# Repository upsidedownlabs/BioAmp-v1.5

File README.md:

# BioAmp v1.5

BioAmp v1.5 is a single chip Bio-potential amplifier for recording any Bio-potential signal non-invasively. It's compatible with [Backyard Brains Spike Recorder](https://backyardbrains.com/products/spikerecorder), which you can use to record and visualize all the Bio-potential signals. 

## Hardware

BioAmp v1.5 has been created using [KiCad](https://www.kicad.org/) and all the design files can be found under [hardware](hardware/) folder, including production [Gerber](hardware/gerbers) files. Images below shows a quick overview of the hardware design.

| Front             |  Back |
| :-------------------------: | :-------------------------: |
|   |  |

|Assembled PCB|
|:--:|
||

| Dimensions             |  Schematic  |
| :-------------------------: | :-------------------------: |
| 32x60mm  |  |

| Licenses Facts              |  OSHWA Certification |
| :-------------------------: | :-------------------------: |
|   |  |

## License
#### Hardware
CERN Open Hardware License Version 2 - Strongly Reciprocal ([CERN-OHL-S-2.0](https://spdx.org/licenses/CERN-OHL-S-2.0.html)).

#### Software
MIT open source [license](http://opensource.org/licenses/MIT).

#### Documentation:
<br />This work is licensed under a <a rel="license" href="http://creativecommons.org/licenses/by/4.0/">Creative Commons Attribution 4.0 International License</a>.

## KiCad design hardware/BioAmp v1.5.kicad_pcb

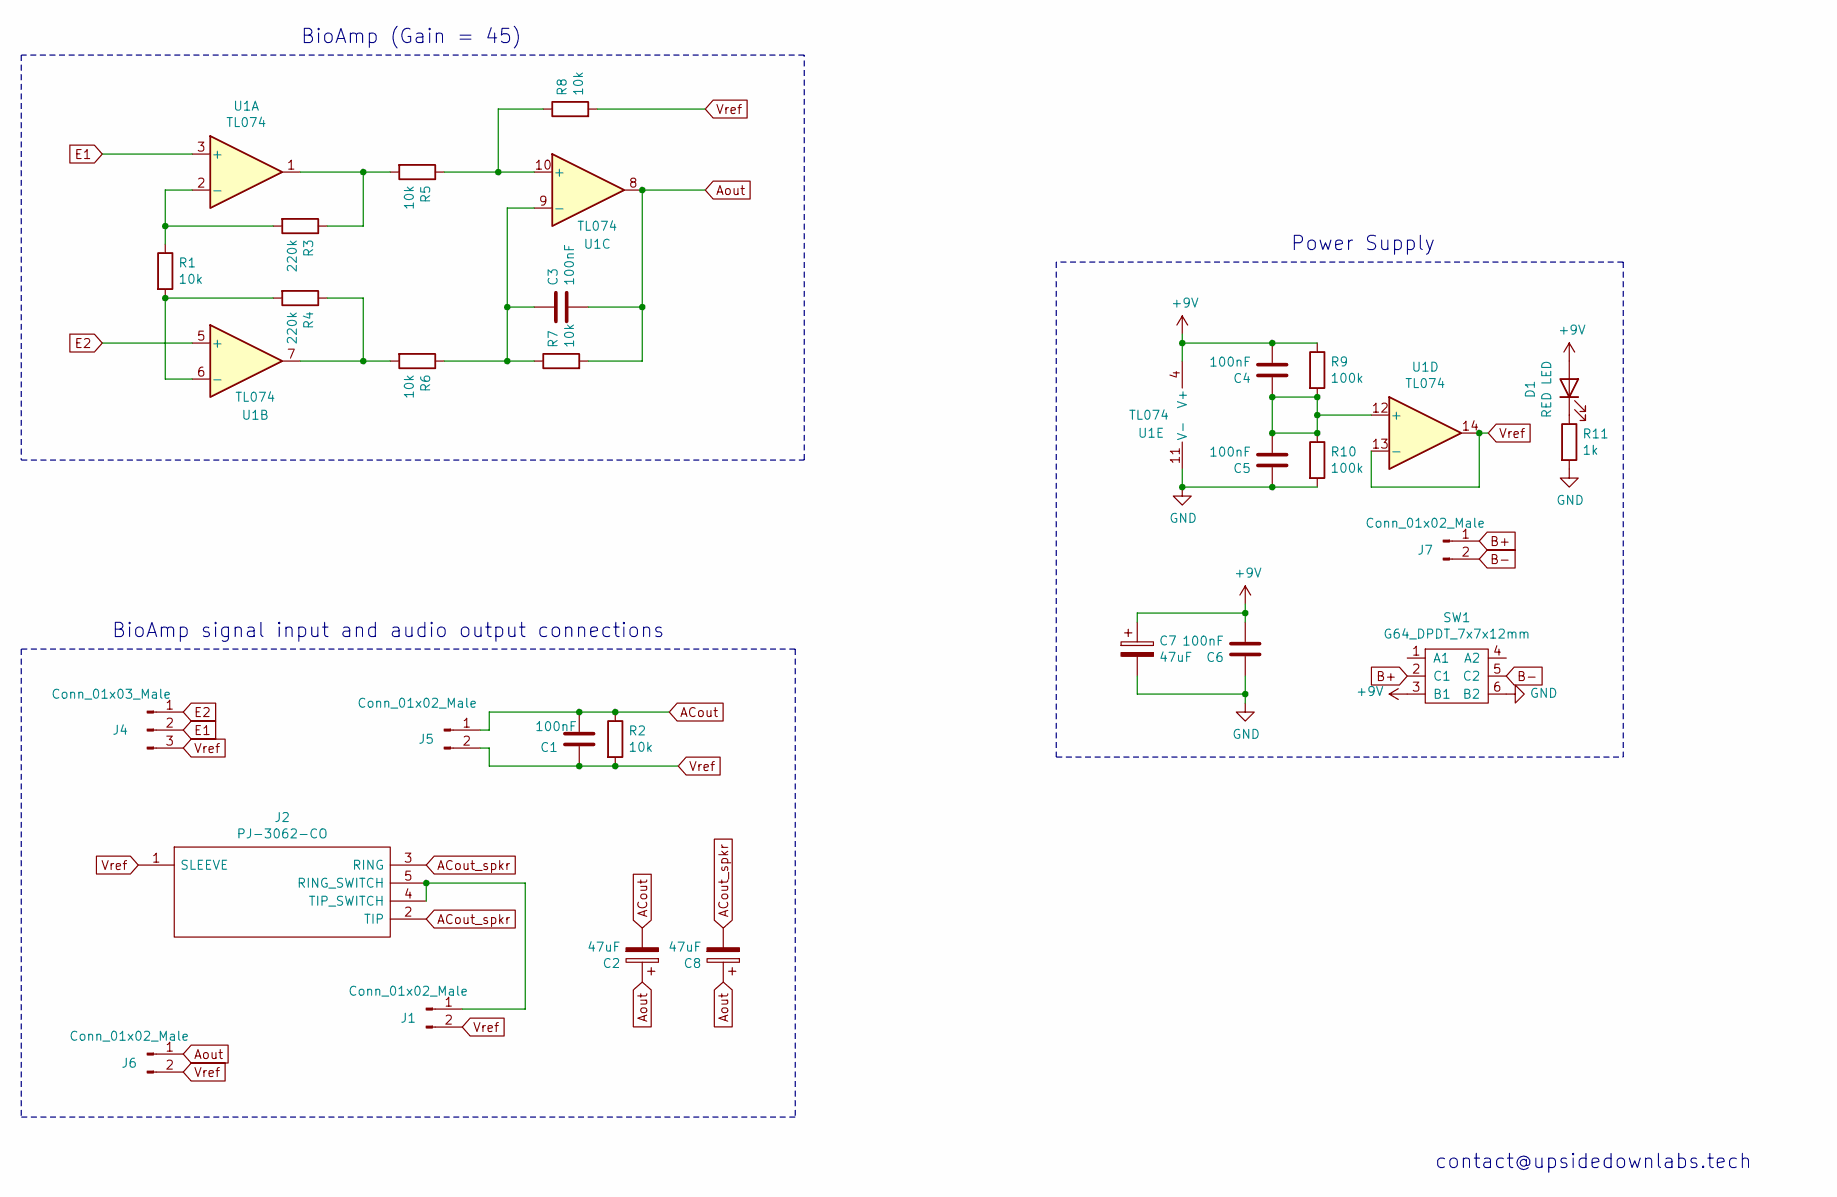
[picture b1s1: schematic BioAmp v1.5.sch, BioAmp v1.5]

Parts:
C1, C3, C4, C5, C6: 100nF; C_Disc_D3.8mm_W2.6mm_P2.50mm
C2, C7, C8: 47uF; CP_Radial_D5.0mm_P2.50mm
D1: RED LED; LED_D5.0mm
J1, J5, J6, J7: Conn_01x02_Male; PinHeader_1x02_P2.54mm_Vertical
J2: PJ-3062-CO; PJ3062CO; Manufacturer_Part_Number PJ-3062-CO
J4: Conn_01x03_Male; PinHeader_1x03_P2.54mm_Vertical
R1, R2, R5, R6, R7, R8: 10k; R_Axial_DIN0207_L6.3mm_D2.5mm_P7.62mm_Horizontal
R3, R4: 220k; R_Axial_DIN0207_L6.3mm_D2.5mm_P7.62mm_Horizontal
R9, R10: 100k; R_Axial_DIN0207_L6.3mm_D2.5mm_P7.62mm_Horizontal
R11: 1k; R_Axial_DIN0207_L6.3mm_D2.5mm_P7.62mm_Horizontal
SW1: G64_DPDT_7x7x12mm
U1: TL074; DIP-14_W7.62mm_Socket_LongPads

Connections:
+9V: C4.2, C6.2, C7.1, D1.2 (A), R9.1, SW1.3 (B1), U1.4 (V+); also elsewhere on the board
ACout: C1.2, C2.2, J5.1, R2.1; also elsewhere on the board
ACout_spkr: C8.2, J2.2 (TIP), J2.3 (RING)
Aout: C2.1, C3.2, C8.1, J6.1, R7.2, U1.8
B+: J7.1, SW1.2 (C1); also elsewhere on the board
B-: J7.2, SW1.5 (C2); also elsewhere on the board
E1: J4.2, U1.3 (+); also elsewhere on the board
E2: J4.1, U1.5 (+); also elsewhere on the board
GND: C5.1, C6.1, C7.2, R10.2, R11.2, SW1.6 (B2), U1.11 (V-); also elsewhere on the board
unnamed: C3.1, R6.1, R7.1, U1.9 (-)
unnamed: C4.1, C5.2, R9.2, R10.1, U1.12 (+)
unnamed: D1.1 (K), R11.1
unnamed: J1.1, J2.4 (TIP_SWITCH), J2.5 (RING_SWITCH)
unnamed: R1.1, R3.2, U1.2 (-)
unnamed: R1.2, R4.2, U1.6 (-)
unnamed: R3.1, R5.2, U1.1
unnamed: R4.1, R6.2, U1.7
unnamed: R5.1, R8.1, U1.10 (+)
Vref: C1.1, J1.2, J2.1 (SLEEVE), J4.3, J5.2, J6.2, R2.2, R8.2, U1.13 (-), U1.14; also elsewhere on the board

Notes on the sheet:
BioAmp (Gain = 45)
Power Supply
BioAmp signal input and audio output connections
contact@upsidedownlabs.tech

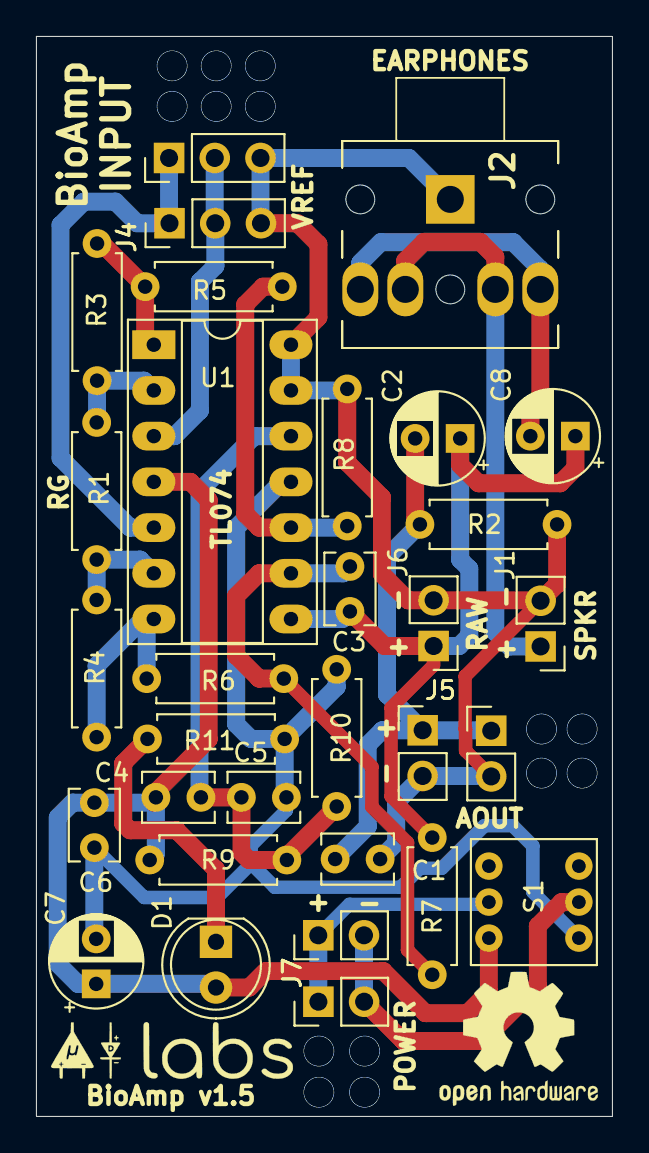
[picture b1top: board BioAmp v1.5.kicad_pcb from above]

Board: 2 copper layers, 32.0 x 60.0 mm, 31 parts (0 on the bottom side), 19 nets.

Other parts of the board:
J4#2: Electode cable; PinHeader_1x03_P2.54mm_Vertical
J5#2: Audio cable; PinHeader_1x02_P2.54mm_Vertical
J7#2: Conn_01x02_Male; PinHeader_1x02_P2.54mm_Vertical
S1: TL2285EE; G64_DPDT

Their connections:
+9V: S1.3; also elsewhere on the board
ACout: J5#2.1; also elsewhere on the board
B+: J7#2.1, S1.2; also elsewhere on the board
B-: J7#2.2, S1.5; also elsewhere on the board
E1: J4#2.2; also elsewhere on the board
E2: J4#2.1; also elsewhere on the board
GND: S1.6; also elsewhere on the board
Vref: J4#2.3, J5#2.2; also elsewhere on the board

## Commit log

2020-11-18 add 1.5.(1,2,3) boards
2020-11-18 fix Readme
2020-11-18 add shematic pdf
2020-11-18 update licence
2020-11-19 fix bottom image reference
2020-11-19 add project zip
2020-11-20 add images
2020-11-20 add v1.5.4 shematic
2020-11-20 add v1.5.4 zip
2020-11-29 add OSH certification mark
2020-11-29 add licenses facts
2020-12-18 Old circuit not required
2020-12-18 Delete Licenses_facts.png image
    Image not required as better svg already available.
2020-12-18 add schematic images
2020-12-18 Update Readme
    Include schematic and more info
2020-12-18 change schematic bg to white
2020-12-18 Update Readme with shields
2020-12-18 Clean repo for new v1.5.5
2020-12-18 Add v1.5.5 images
2020-12-18 Add BioAmp v1.5.5 zip
2020-12-18 Add BioAmp v1.5.5 schematic pdf
2021-03-06 add 3D models
    These are the 3D model files of BioAmp v1.5 which can be used with 3D software like Blender to render some nice looking images.
2021-03-06 add assembly instructions manual
    This will help in the making of BioAmp v1.5 from the DIY kit we sell in Tindie.
2021-03-06 BioAmp v1.5 BOM for reference
2021-03-06 Update schematic
    Updated the capacitor referneces
2021-03-06 BOM csv file
2021-03-06 BioAmp blank PCB image
    purple black PCB for reference purpose.
2021-03-06 Cable connection guide
2021-03-06 Capacitor assembly guide
2021-03-06 IC&LED assembly guide
2021-03-06 Connector&Switches assembly guide
2021-03-06 Resistor assembly guide
2021-03-06 BioAmp v1.5 fully assembled
2021-04-05 Cleanup & Rearrange files
    Initial cleanup for major software update. Awesome Python notebooks and scripts will be added soon :)
2021-07-14 BioAmp v1.5.6 KiCAD PCB
    This version includes minor cosmetic changes,
    this will be the final revision of BioAmp v1.5!
2021-07-14 BioAmp v1.5.6 KiCAD schematic
    This version includes minor cosmetic changes,
    this will be the final revision of BioAmp v1.5!
2021-07-14 BioAmp v1.5.6 gerbers
    This version includes minor cosmetic changes,
    this will be the final revision of BioAmp v1.5!
2021-07-14 BioAmp v1.5.6 gerbers zip
    This version includes minor cosmetic changes,
    this will be the final revision of BioAmp v1.5!
2021-07-14 Re-arrange files
    changing directory structure to increase user accessebility.
2021-07-14 BioAmp v1.5.6 KiCAD hardware files
2021-07-14 BioAmp v1.5.6 KiCAD gerber files
2021-07-14 BioAmp v1.5.6 licence images
2021-07-14 BioAmp v1.5.6 assemled hardware image
2021-07-14 BioAmp v1.5.x schematic images
2021-07-14 BioAmp v1.5.5 Dia diagram images (assembly)
2021-07-14 BioAmp v1.5.5 board images
2021-07-14 BioAmp v1.5.6 front image
    KiCAD render of BioAmp v1.5.6
2021-07-14 BioAmp v1.5.6 back image
    KiCAD render of BioAmp v1.5.6
2021-07-14 BioAmp v1.5.6 dimensions image
2021-07-14 BioAmp v1.5 3D files
2021-07-14 BioAmp v1.5.6 schematic PDF
2021-07-14 BioAmp v1.5.6 assembly instructions
2021-07-14 Update license (BioAmp v1.5.6)
2021-07-14 Update readme (BioAmp v1.5.6)
2021-07-14 remove BOM folder
2021-08-03 Updating...
    Removing unwanted files from the repo.
2021-08-03 BioAmp v1.5.7 hardware files
    Small modification for the holes in this update.
2021-08-03 Interactive BOM
    This HTML file is the interactive BOM of BioAmp v1.5.7
2021-08-03 BioAmp v1.5.7 schematic image
    High contrast and normal picture of BioAmp v1.5.7
2021-08-03 BioAmp v1.5.7 board images
    SVG and PNG of the final BioAmp v1.5.7 board
2021-08-03 Aligator clip files
    SVG files of aligator clips.
2021-08-03 9v battery snap
    SVG files for 9v battery snap.
2021-08-03 3.5mm male jack SVG and PNG
2021-08-03 15. Full kit
    BioAmp v1.5.7 fully assembled kit
2021-08-03 14. Electrode cable
2021-08-03 13. Audio cable
2021-08-03 12. Battery snap
2021-08-03 11. Header pins
2021-08-03 10. Headphone jack
2021-08-03 09. DPDT switch
2021-08-03 08. IC socket
2021-08-03 07. LED
2021-08-03 06. Capacitor 47uf
2021-08-03 05. Capacitor 100nF
2021-08-03 04. Resisitor 220k
2021-08-03 03. Resistor 100k
2021-08-03 Resistor 10k
2021-08-03 01. Resistor 1k
2021-08-03 00. Blank PCB
2021-08-03 BioAmp v1.5.7 3D STEP file
2021-08-03 BioAmp v1.5.7 schematic
2021-08-03 BioAmp v1.5 assembly guide
2021-08-03 Fully assembled BioAmp v1.5.7 PCB
2022-01-18 Update assembly instruction guide
    IC holder was shows incorrectly, it has been fixed now :)
2022-01-18 Update graphics
    IC holder was shown incorrectly, it has been fixed now :)
2022-01-18 Update graphics

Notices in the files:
README.md:
Open Source Licenses Facts
